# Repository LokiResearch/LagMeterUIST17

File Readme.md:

# Description

## electronicBoard

Contains the Eagle files to replicate the lagmeter shield for Arduino Leonardo.

A [shopping basket](http://www.digikey.fr/short/qtt791) with the list of components to buy is ready for Digikey (also available as a [CSV file](electronicBoard/digikey.csv)).

## LagmeterLeonardo

Contains the Arduino code to run on an Arduino Leonardo board with the above shield.

Requires to install [HID-Project](https://github.com/NicoHood/HID/) first.

## TurboHID

Contains C++ source code to communicate with the Arduino Leonardo using raw HID.

You have to install [libpointing](http://libpointing.org) first (used for the timestamps).

To compile the library run ```qmake && make```

On Windows, the library is provided in the external folder.

## BasicLogger

Code for logging data coming from the Arduino

Successfully compile using Qt 5.15.1 MSCV2015 64 bits in release mode.

## ReplicationCppQt && ReplicationCppGLUT

Code for producing tables 4, 5 & 6 in the paper. Compile using ```qmake && make```

Edit ```config.cfg``` to provide the URI for your mouse.

Directly pass the config file as a parameter for the GLUT application and use ```-c config.cfg``` for the Qt application.

## parser

Python code to parse the log files and compute stats.

Example: ```./parse-log --start piezo yourlogfile```

You have to correct the reported values according to what is described in the paper: "Intermediate latency values were computed by subtracting the host computer piezo time from the considered event time (libpointing, system, toolkit, repaint or screen), adding 5.7 ms and further adding 0.7 ms for the initial communication between the Arduino and the host computer." (page 5). Read the paper for more details.

## FlashApps

Code for producing Table 7 in the paper.

## UISTdemo

Android code used for the UIST demo showing the measure of latency while the user is interacting with an application. The lagmeter is connected to the Android device.

## Related publication

```
@inproceedings{10.1145/3126594.3126606,
    author = {Casiez, G\'{e}ry and Pietrzak, Thomas and Marchal, Damien and Poulmane, S\'{e}bastien and Falce, Matthieu and Roussel, Nicolas},
    title = {Characterizing Latency in Touch and Button-Equipped Interactive Systems},
    year = {2017},
    isbn = {9781450349819},
    publisher = {Association for Computing Machinery},
    address = {New York, NY, USA},
    url = {https://doi.org/10.1145/3126594.3126606},
    doi = {10.1145/3126594.3126606},
    abstract = {We present a low cost method to measure and characterize the end-to-end latency when using a touch system (tap latency) or an input device equipped with a physical button. Our method relies on a vibration sensor attached to a finger and a photo-diode to detect the screen response. Both are connected to a micro-controller connected to a host computer using a low-latency USB communication protocol in order to combine software and hardware probes to help determine where the latency comes from. We present the operating principle of our method before investigating the main sources of latency in several systems. We show that most of the latency originates from the display side. Our method can help application designers characterize and troubleshoot latency on a wide range of interactive systems.},
    booktitle = {Proceedings of the 30th Annual ACM Symposium on User Interface Software and Technology},
    pages = {29–39},
    numpages = {11},
    keywords = {toolkits, measurement tools, measure, latency, lag},
    location = {Qu\'{e}bec City, QC, Canada},
    series = {UIST '17}
}
```

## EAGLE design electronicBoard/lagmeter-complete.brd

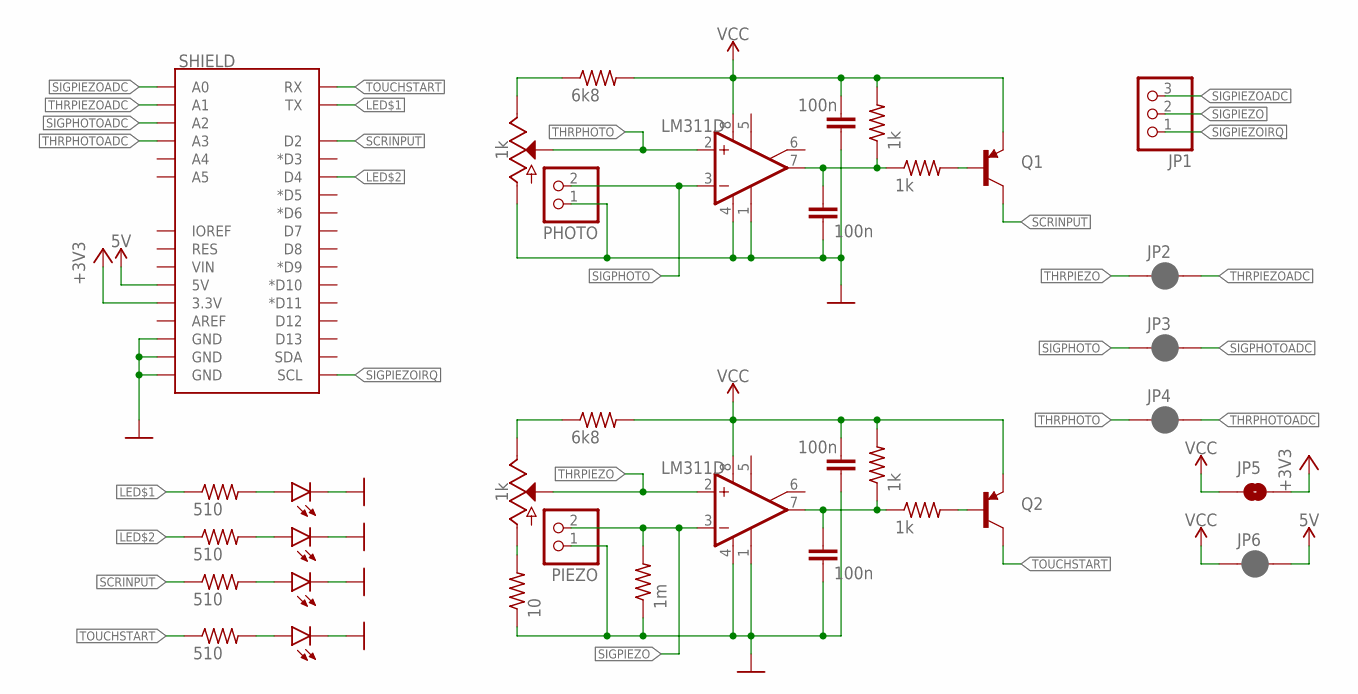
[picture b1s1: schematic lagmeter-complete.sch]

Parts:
C1, C2, C3, C4: 100n; C0805
D1, D2, D3, D4: LED1206; LED-1206
IC1, IC2: LM311D; SO08
JP1: PINHD-1X3; 1X03
JP2, JP3, JP4: JUMPER-SMT_2_NC_PASTE_SILK; SMT-JUMPER_2_NC_PASTE_SILK
JP5: JUMPER-SMT_2_NO_NO-SILK; SMT-JUMPER_2_NO_NO-SILK
JP6: JUMPER-SMT_2_NC_PASTE_NO-SILK; SMT-JUMPER_2_NC_PASTE_NO-SILK
PHOTO: PINHD-1X2; 1X02
PIEZO: PINHD-1X2; 1X02
Q1, Q2: TRANSISTOR_PNPSMD; SOT23-3
R1, R2: 6k8; R0603
R3, R4, R5, R6: 1k; R0603
R7, R8, R9, R10: 510; R0603
R11: 1m; R0603
R12: 10; R0603
SHIELD: ARDUINO_UNO_R3_SHIELDBASIC; UNO_R3_SHIELD
VR1, VR2: 1k; POT-PTH-ALPS

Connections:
5V: JP6.2, SHIELD.5V
+3V3: JP5.2, SHIELD.3.3V
GND: C1.2, C2.2, C3.2, C4.2, D1.C, D2.C, D3.C, D4.C, IC1.1 (GND), IC1.4 (V-), IC2.1 (GND), IC2.4 (V-), PHOTO.1, PIEZO.1, R11.1, R12.1, SHIELD.GND@0 (GND), SHIELD.GND@1 (GND), SHIELD.GND@2 (GND), VR1.P$3 (A)
LED$1: R9.1, SHIELD.TX
LED$2: R7.1, SHIELD.D4
MAXTHR: R2.1, VR2.P$1 (E)
MINTHR: R12.2, VR2.P$3 (A)
unnamed: D1.A, R9.2
unnamed: C2.1, IC1.7 (OUT), R3.1, R4.1
unnamed: D2.A, R7.2
unnamed: D3.A, R8.2
unnamed: Q1.1 (B), R3.2
unnamed: C4.1, IC2.7 (OUT), R5.1, R6.1
unnamed: Q2.1 (B), R5.2
unnamed: D4.A, R10.2
REFPHOTO: R1.1, VR1.P$1 (E)
SCRINPUT: Q1.3 (C), R8.1, SHIELD.D2
SIGPHOTO: IC1.3 (-IN), JP3.1, PHOTO.2
SIGPHOTOADC: JP3.2, SHIELD.A2
SIGPIEZO: IC2.3 (-IN), JP1.2, PIEZO.2, R11.2
SIGPIEZOADC: JP1.3, SHIELD.A0
SIGPIEZOIRQ: JP1.1, SHIELD.SCL
THRPHOTO: IC1.2 (+IN), JP4.1, VR1.P$2 (S)
THRPHOTOADC: JP4.2, SHIELD.A3
THRPIEZO: IC2.2 (+IN), JP2.1, VR2.P$2 (S)
THRPIEZOADC: JP2.2, SHIELD.A1
TOUCHSTART: Q2.3 (C), R10.1, SHIELD.RX
VCC: C1.1, C3.1, IC1.8 (V+), IC2.8 (V+), JP5.1, JP6.1, Q1.2 (E), Q2.2 (E), R1.2, R2.2, R4.2, R6.2

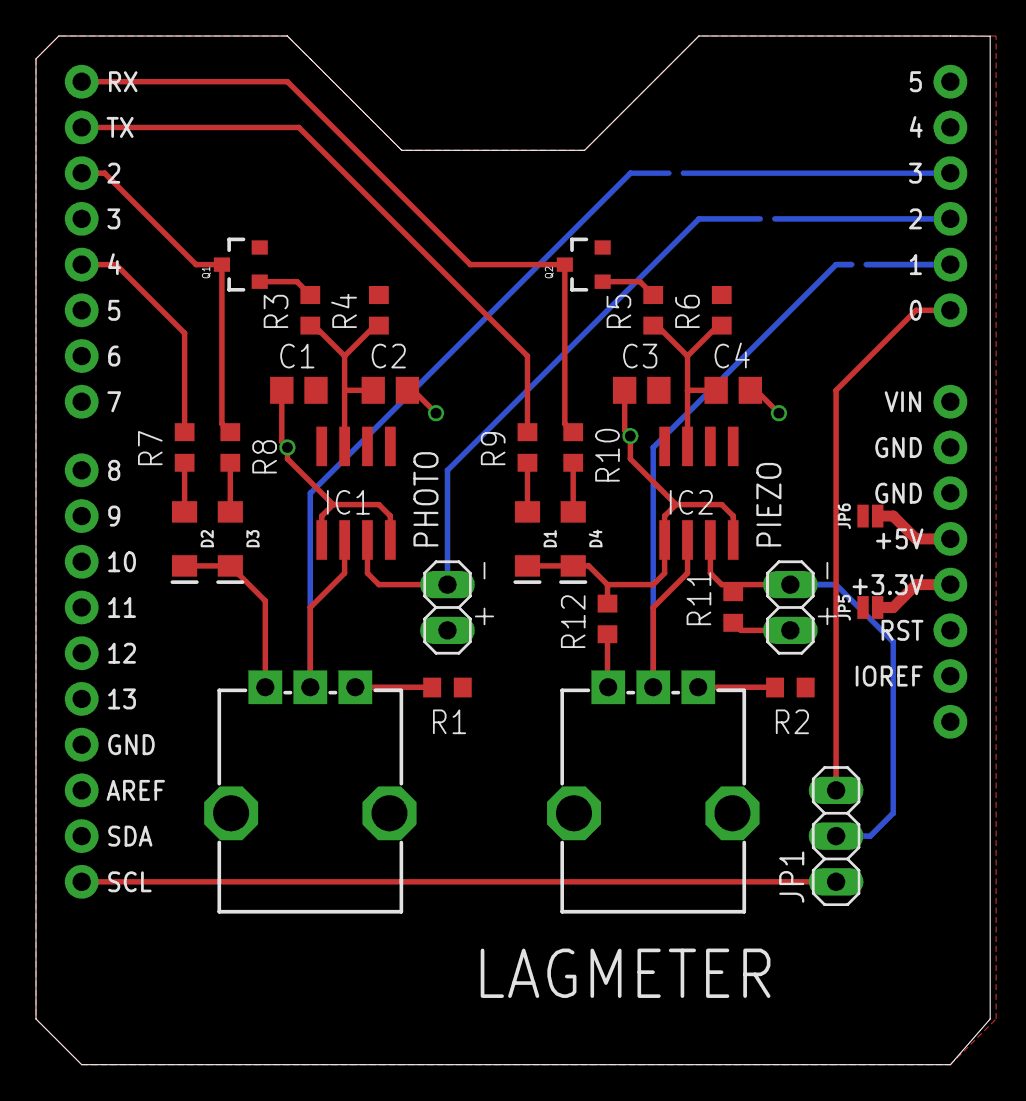
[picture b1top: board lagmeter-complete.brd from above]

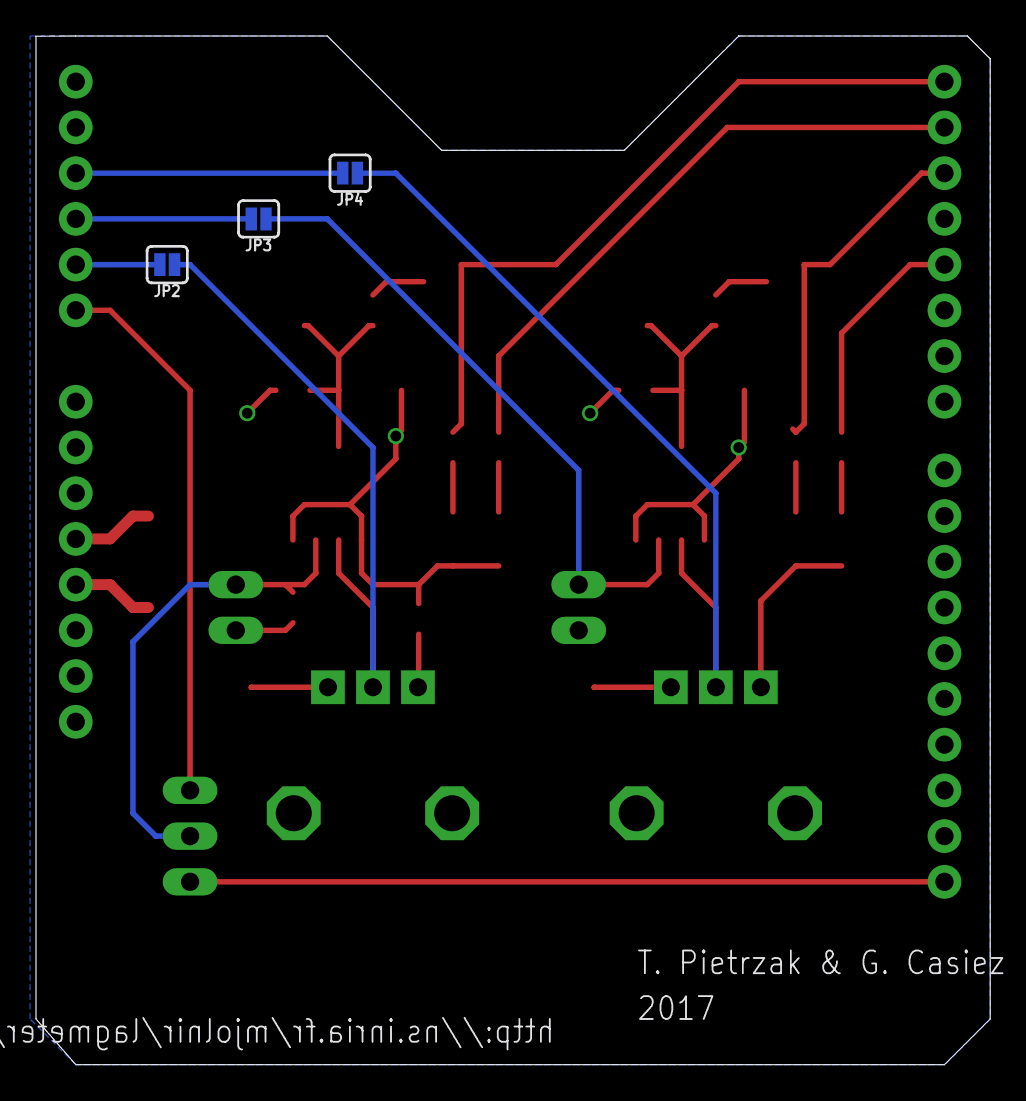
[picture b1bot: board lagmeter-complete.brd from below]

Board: 2 copper layers, 53.0 x 57.1 mm, 35 parts (3 on the bottom side), 28 nets.

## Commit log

2025-10-17 Supporting homebrew on arm

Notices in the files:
parts and their libraries:
SparkFun-LED: Licensing: Creative Commons ShareAlike 4.0 International - https://creativecommons.org/licenses/by-sa/4.0
